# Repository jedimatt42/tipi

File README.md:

# TIPI

(Pronounced tip-ee)

Turn a Raspberry PI and some glue hardware into a TI Disk Drive and Network interface. 

Keep it open for further device extension.

## Branching

(For end users starting from an SD card image, you are already on the correct branch)

- End users must be on one of the `_release` branches for physical TIPI
- `main` branch is full of stuff that doesn't work, won't upgrade correctly, and certainly won't downgrade
- `main` branch is expert mode only

Branches:

```
  main - current development for latest Raspberry PI OS
  bookworm_release - Current release branch based on Raspberry PI OS 12 - bookworm
  bullseye_release - (legacy) end of life, as new bookworm_release branch is available
  buster_dev - (legacy) for patching upstream of buster_release
  buster_release - (legacy) for Raspberry PI 2W - 4B+ or Qemu use.
```

## Documentation

Please refer to the [wiki](https://github.com/jedimatt42/tipi/wiki)

## License 

The hardware design files and TI-99 DSR ROM code are in the [hardware](hardware) folder and free for use under the [UNLICENSE.txt](hardware/UNLICENSE.txt) 

The remaining software contained in this repository are licensed under the terms of [GPLv3](https://www.gnu.org/licenses/quick-guide-gplv3.en.html)

These files are part of TIPI.

TIPI is free hardware design and software: you can redistribute it and/or modify it under the terms of the GNU General Public License as published by the Free Software Foundation, either version 3 of the License, or (at your option) any later version.

TIPI is distributed in the hope that it will be useful, but WITHOUT ANY WARRANTY; without even the implied warranty of MERCHANTABILITY or FITNESS FOR A PARTICULAR PURPOSE.  See the GNU General Public License for more details.

You should have received a copy of the GNU General Public License along with TIPI SD Card Image.  If not, see [GNU Licenses](http://www.gnu.org/licenses/).

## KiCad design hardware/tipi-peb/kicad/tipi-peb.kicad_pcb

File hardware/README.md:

# Hardare design files for TIPI board and ROM driver software

This package below contains the hardware design files. These are un-encumbered open license files you can all do whatever you want with...

* tipi-peb - contains the PCB designs for the Periphal Expansion Box variant of the board. 
  * gerbers - artifacts for PCB fabrication
  * kicad - pcb schematic and layout design files for KiCad
  * ise - the verilog - Xilinx ISE 14.1 project files (use this with tipi-sideport design also)
* tipi-sideport - contains the PCB designs for the sideport board
  * gerbers - artifacts for PCB fabrication
  * kicad - pcb schematic and layout design files for KiCad
* tipi-speech - contains the PCB designs for the Speech Synthsizer Box variant of the TIPI board. 
  * gerbers - artifacts for PCB fabrication
  * kicad - pcb schematic and layout design files for KiCad
  * ise - the verilog - Xilinx ISE 14.1 project files (combined 32k and TIPI decoding)
* dsr - the ROM driver software for messaging to the PI and general DISK like behavior.

See [UNLICENSE.txt](UNLICENSE.txt)

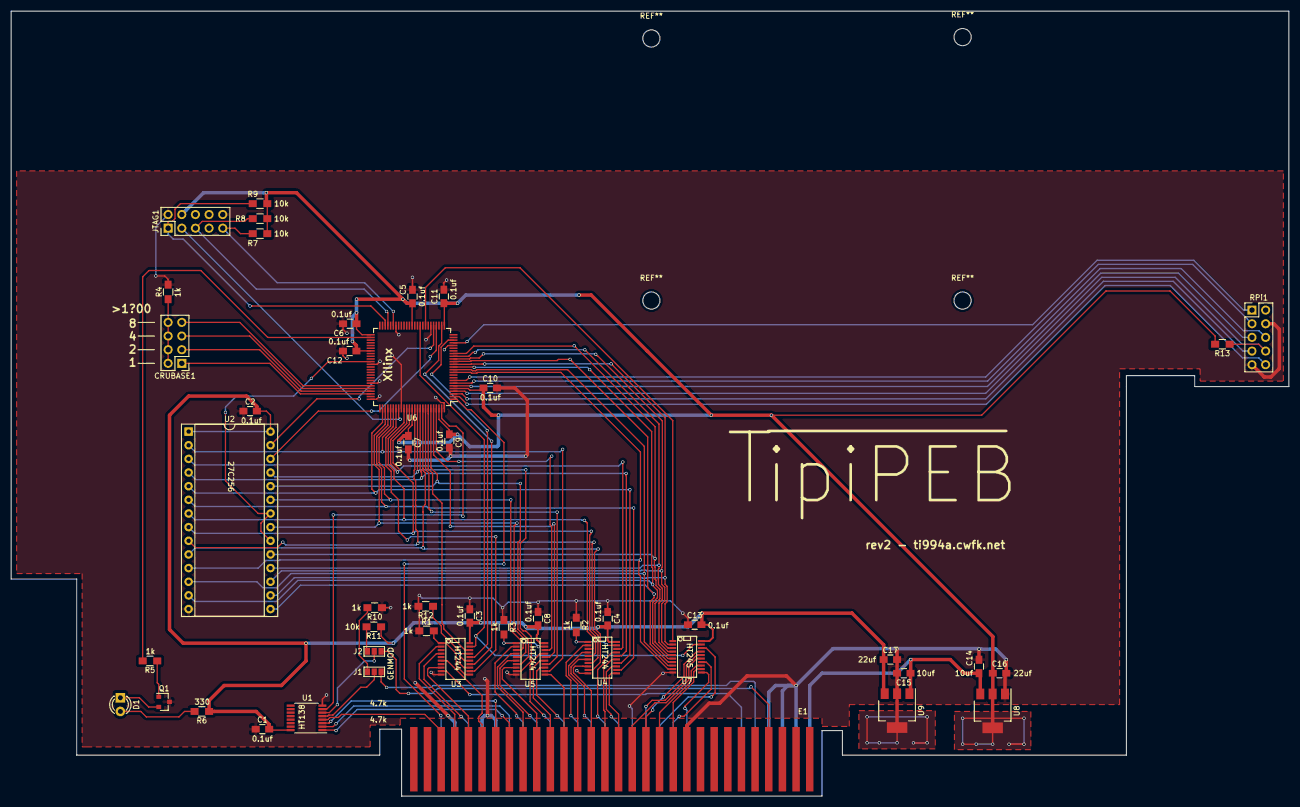
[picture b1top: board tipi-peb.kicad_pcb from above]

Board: 2 copper layers, 237.7 x 146.1 mm, 47 parts (0 on the bottom side), 102 nets.

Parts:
C1, C2, C3, C4, C5, C6, C7, C8, C9, C10, C11, C12, C13: 0.1uf; C_0805_HandSoldering
C14, C15: 10uf; C_0805_HandSoldering
C16, C17: 22uf; C_0805_HandSoldering
CRUBASE1: CONN_02X04; Pin_Header_Straight_2x04_Pitch2.54mm
D1: LED_ALT; LED_D3.0mm
E1: TiPEBEdge; ti99-peb-edge
J1, J2: GS3
JTAG1: AVR-JTAG-10; Pin_Header_Straight_2x05_Pitch2.54mm
Q1: Q_NPN_BCE; SOT-23
R1, R2, R3, R4, R5, R10, R12: 1k; R_0805_HandSoldering
R6: 330; R_0805_HandSoldering
R7, R8, R9, R11, R13: 10k; R_0805_HandSoldering
RPi1: RPI_CONN_02X05; Pin_Header_Straight_2x05_Pitch2.54mm
U1: 74HCT138; TSSOP-16_4.4x5mm_Pitch0.65mm
U2: 27C256; DIP-28_W15.24mm_Socket
U3, U4, U5: 74HCT244; SSOP-20
U6: XC95144XL-TQ100; TQFP-100_14x14mm_Pitch0.5mm
U7: 74HCT245; SSOP-20
U8: LM1117-3.3; SOT-223-3_TabPin2
U9: LM7805_TO220; SOT-223-3_TabPin2

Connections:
+3V3: C5.1, C6.1, C7.1, C9.1, C10.1, C11.1, C12.1, C16.1, JTAG1.4, R7.2, R8.2, R9.2, R13.2, U6.5, U6.26, U6.38, U6.51, U6.57, U6.88, U6.98, U8.2
+5V: C1.2, C2.2, C3.2, C4.2, C8.2, C13.2, C17.1, R6.1, R11.1, U1.16, U2.1, U2.28, U3.20, U4.20, U5.20, U7.20, U9.3
+8V: C14.1, C15.1, E1.1, U8.3, U9.1
B_A0: U5.18, U6.97
B_A1: U5.16, U6.96
B_A2: U5.14, U6.93
B_A3: U2.2, U5.12, U6.81
B_A4: U2.23, U5.3, U6.80
B_A5: U2.21, U5.5, U6.78
B_A6: U2.24, U5.7, U6.95
B_A7: U2.25, U5.9, U6.90
B_A8: U2.3, U4.18, U6.86
B_A9: U2.4, U4.16, U6.91
B_A10: U2.5, U4.14, U6.77
B_A11: U2.6, U4.12, U6.79
B_A12: U2.7, U4.3, U6.85
B_A13: U2.8, U4.5, U6.87
B_A14: U2.9, U4.7, U6.89
B_A15: U2.10, U4.9, U6.92
B_CRUCLK: U3.16, U6.23
B_DBIN: U3.12, U6.82
B_MEMEN: U1.7, U6.99
B_PH3: U3.14, U6.27
B_WE: U3.18, U6.94
CRUB_0: CRUBASE1.8, U6.70
CRUB_1: CRUBASE1.7, U6.71
CRUB_2: CRUBASE1.6, U6.72
CRUB_3: CRUBASE1.5, U6.73
DB_DIR: U6.33, U7.1
DB_EN: U3.19, U6.35, U7.19
DSR_B0: U2.26, U6.29
DSR_B1: U2.27, U6.30
DSR_EN: U2.20, U2.22, U6.61
GND: C1.1, C2.1, C3.1, C4.1, C5.2, C6.2, C7.2, C8.1, C9.2, C10.2, C11.2, C12.2, C13.1, C14.2, C15.2, C16.2, C17.2, E1.3, E1.5, E1.7, E1.20, E1.27, E1.47, E1.49, E1.53, JTAG1.2, JTAG1.10, Q1.3, R1.1, R2.1, R3.1, R4.2, R10.1, R12.2, RPi1.5, RPi1.9, U1.8, U2.14, U3.10, U4.10, U5.10, U6.21, U6.31, U6.44, U6.62, U6.69, U6.75, U6.84, U6.100, U7.10, U8.1, U9.2
JTAG_TCK: JTAG1.1, R9.1, U6.48
JTAG_TDI: JTAG1.9, R7.1, U6.45
JTAG_TDO: JTAG1.3, U6.83
JTAG_TMS: JTAG1.5, R8.1, U6.47
LED0: R5.2, U6.52
unnamed: CRUBASE1.1, CRUBASE1.2, CRUBASE1.3, CRUBASE1.4, R4.1
unnamed: D1.1, Q1.2
unnamed: D1.2, R6.2
unnamed: J1.1, R10.2
unnamed: J1.2, U1.5
unnamed: J2.1, R11.2
unnamed: J2.2, U1.6
unnamed: Q1.1, R5.1
unnamed: R1.2, U3.1, U3.11
unnamed: R2.2, U4.1, U4.19
unnamed: R3.2, U5.1, U5.19
unnamed: R12.1, U3.13, U3.15, U3.17
RDBENA: E1.11, U3.9
R_CLK: RPi1.1, U6.22
R_DC: RPi1.6, U6.2
R_DIN: R13.1, RPi1.7, U6.4
R_DOUT: RPi1.8, U6.7
R_LE: RPi1.3, U6.6
R_RESET: RPi1.4, U6.3
R_RT: RPi1.2, U6.8
TI_A0: E1.43, U5.2
TI_A1: E1.44, U5.4
TI_A2: E1.41, U5.6
TI_A3: E1.42, U5.8
TI_A4: E1.39, U5.17
TI_A5: E1.40, U5.15
TI_A6: E1.37, U5.13
TI_A7: E1.38, U5.11
TI_A8: E1.35, U4.2
TI_A9: E1.36, U4.4
TI_A10: E1.33, U4.6
TI_A11: E1.34, U4.8
TI_A12: E1.31, U4.17
TI_A13: E1.32, U4.15
TI_A14: E1.29, U4.13
TI_A15: E1.30, U4.11
TI_AMA: E1.46, U1.1
TI_AMB: E1.45, U1.2
TI_AMC: E1.48, U1.3
TI_AMD: E1.8, J2.3
TI_AME: E1.9, J1.3
TI_CRUCLK: E1.51, U3.4
TI_CRUIN: E1.55, U6.1
TI_D0: E1.28, U7.15
TI_D1: E1.25, U7.16
TI_D2: E1.26, U7.17
TI_D3: E1.23, U7.18
TI_D4: E1.24, U7.13
TI_D5: E1.21, U7.14
TI_D6: E1.22, U7.12
TI_D7: E1.19, U7.11
TI_DBIN: E1.52, U3.8
TI_MEMEN: E1.56, U1.4
TI_PH3: E1.50, U3.6
TI_WE: E1.54, U3.2
TP_D0: U2.11, U6.11, U7.9
TP_D1: U2.12, U6.12, U7.8
TP_D2: U2.13, U6.13, U7.6
TP_D3: U2.15, U6.15, U7.7
TP_D4: U2.16, U6.14, U7.2
TP_D5: U2.17, U6.16, U7.3
TP_D6: U2.18, U6.17, U7.4
TP_D7: U2.19, U6.18, U7.5

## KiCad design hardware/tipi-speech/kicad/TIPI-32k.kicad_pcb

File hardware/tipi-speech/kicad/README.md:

Hardare design files for VS-TIPI board

This package below contains the hardware design files. These are un-encumbered open license files you can all do whatever you want with...

    vs-tipi - contains the PCB designs for the Speech Synthsizer variant of the board.
        gerbers - artifacts for PCB fabrication
        kicad - pcb schematic and layout design files for KiCad
        ise - the verilog - Xilinx ISE 14.1 project files (use this with tipi-sideport design also)

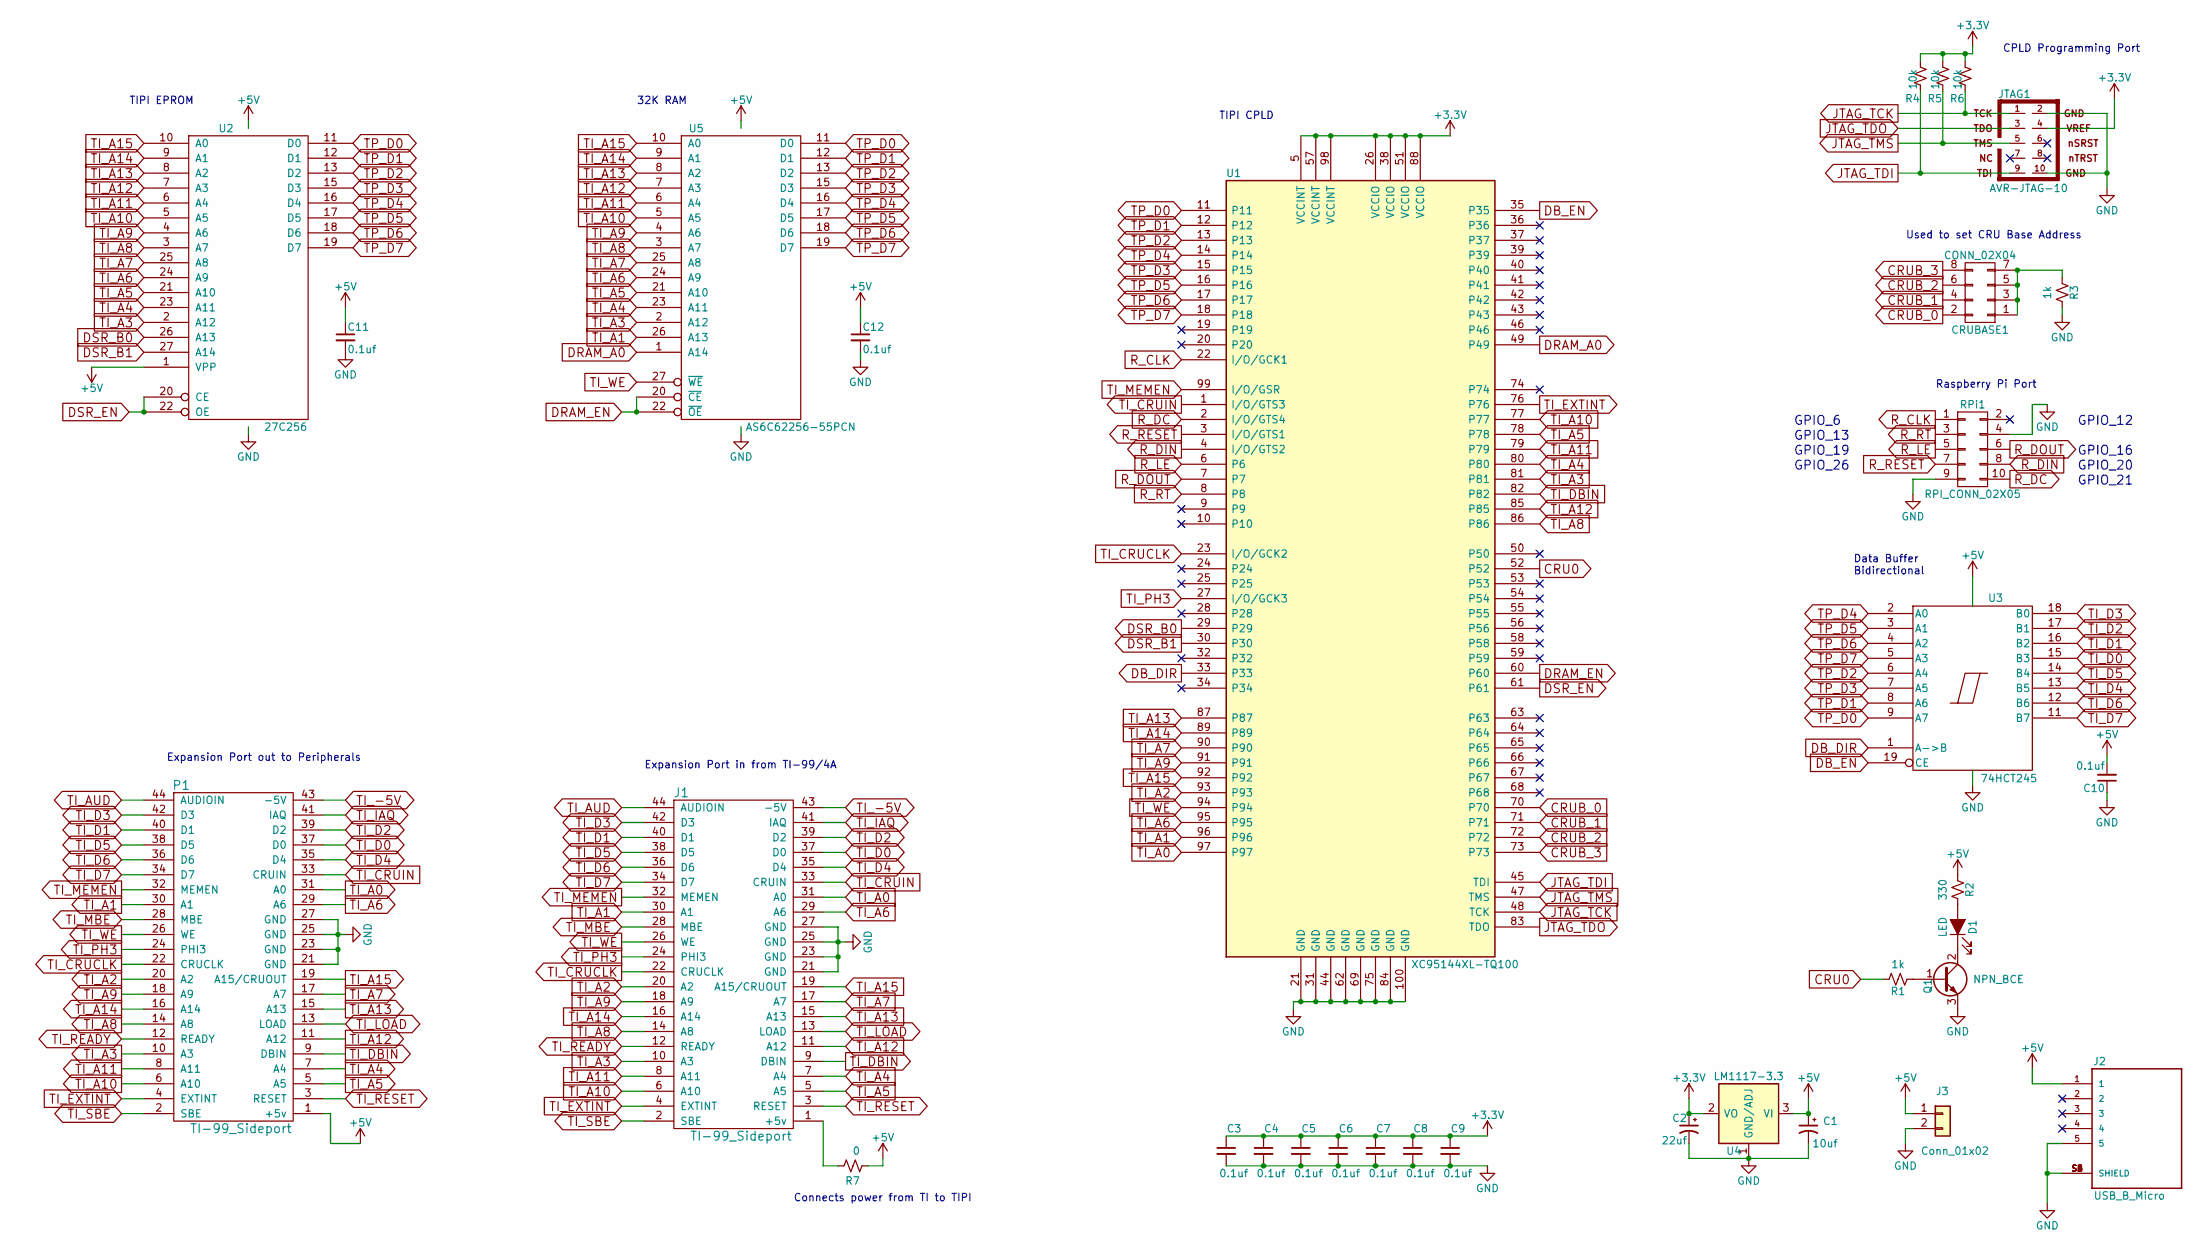
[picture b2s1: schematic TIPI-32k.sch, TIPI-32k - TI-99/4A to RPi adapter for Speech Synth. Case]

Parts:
C1: 10uf; C_0805_HandSoldering; LCSC C15850
C2: 22uf; C_0805_HandSoldering; LCSC C45783
C3, C6, C12: 0.1uf; C_0805_HandSoldering; LCSC C49678
C4, C5, C7, C8, C9, C10, C11: 0.1uf; C_0805_HandSoldering
CRUBASE1: CONN_02X04; Pin_Header_Straight_2x04_Pitch2.54mm
D1: LED; LED_D3.0mm
J1: TI-99_Sideport; ti99-exp-edge
J2: USB_B_Micro; AMPHENOL_10118194-0001LF; LCSC C132563
J3: Conn_01x02; PinHeader_1x02_P2.54mm_Horizontal
JTAG1: AVR-JTAG-10; IDC_Header_Straight_10pins
P1: TI-99_Sideport; ti99-exp-edge
Q1: NPN_BCE; SOT-23; LCSC C31776
R1, R3: 1k; R_0805_HandSoldering; LCSC C17513
R2: 330; R_0805_HandSoldering; LCSC C17630
R4, R5: 10k; R_0805_HandSoldering; LCSC C17414
R6: 10k; R_0805_HandSoldering
R7: 0; C_0805_HandSoldering
RPi1: RPI_CONN_02X05; IDC_Header_Straight_10pins
U1: XC95144XL-TQ100; TQFP-100_14x14mm_Pitch0.5mm; LCSC C45126
U2: 27C256; DIP-28_W15.24mm_Socket
U3: 74HCT245; SSOP-20; LCSC C5980
U4: LM1117-3.3; SOT-223; LCSC C23984
U5: AS6C62256-55PCN; DIP-28_W15.24mm_Socket

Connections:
+3V3: C2.1, C3.1, C4.1, C5.1, C6.1, C7.1, C8.1, C9.1, JTAG1.4, R4.2, R5.2, R6.2, U1.5 (VCCINT), U1.26 (VCCIO), U1.38 (VCCIO), U1.51 (VCCIO), U1.57 (VCCINT), U1.88 (VCCIO), U1.98 (VCCINT), U4.2 (VO), U4.4 (VO)
+5V: C1.1, C10.2, C11.1, C12.1, J2.1, J3.1, P1.1 (+5v), R2.1, R7.2, U2.1 (VPP), U2.28 (VCC), U3.20 (VCC), U4.3 (VI), U5.28 (VCC)
CRU0: R1.2, U1.52
CRUB_0: CRUBASE1.2, U1.70
CRUB_1: CRUBASE1.4, U1.71
CRUB_2: CRUBASE1.6, U1.72
CRUB_3: CRUBASE1.8, U1.73
DB_DIR: U1.33, U3.1 (A->B)
DB_EN: U1.35, U3.19 (CE)
DRAM_A0: U1.49, U5.1 (A14)
DRAM_EN: U1.60, U5.20 (~CE), U5.22 (~OE)
DSR_B0: U1.29, U2.26 (A13)
DSR_B1: U1.30, U2.27 (A14)
DSR_EN: U1.61, U2.20 (CE), U2.22 (OE)
GND: C1.2, C2.2, C3.2, C4.2, C5.2, C6.2, C7.2, C8.2, C9.2, C10.1, C11.2, C12.2, J1.21 (GND), J1.23 (GND), J1.25 (GND), J1.27 (GND), J2.5, J2.S1 (SHIELD), J2.S2 (SHIELD), J2.S3 (SHIELD), J2.S4 (SHIELD), J2.S5 (SHIELD), J2.S6 (SHIELD), J3.2, JTAG1.2, JTAG1.10, P1.21 (GND), P1.23 (GND), P1.25 (GND), P1.27 (GND), Q1.3 (E), R3.2, RPi1.4, RPi1.9, U1.21 (GND), U1.31 (GND), U1.44 (GND), U1.62 (GND), U1.69 (GND), U1.75 (GND), U1.84 (GND), U1.100 (GND), U2.14 (GND), U3.10 (GND), U4.1 (GND/ADJ), U5.14 (GND)
JTAG_TCK: JTAG1.1, R6.1, U1.48 (TCK)
JTAG_TDI: JTAG1.9, R4.1, U1.45 (TDI)
JTAG_TDO: JTAG1.3, U1.83 (TDO)
JTAG_TMS: JTAG1.5, R5.1, U1.47 (TMS)
unnamed: CRUBASE1.1, CRUBASE1.3, CRUBASE1.5, CRUBASE1.7, R3.1
unnamed: D1.1 (K), Q1.2 (C)
unnamed: D1.2 (A), R2.2
unnamed: J1.1 (+5v), R7.1
unnamed: Q1.1 (B), R1.1
R_CLK: RPi1.1, U1.22 (I/O/GCK1)
R_DC: RPi1.10, U1.2 (I/O/GTS4)
R_DIN: RPi1.8, U1.4 (I/O/GTS2)
R_DOUT: RPi1.6, U1.7
R_LE: RPi1.5, U1.6
R_RESET: RPi1.7, U1.3 (I/O/GTS1)
R_RT: RPi1.3, U1.8
TI_-5V: J1.43 (-5V), P1.43 (-5V)
TI_A0: J1.31 (A0), P1.31 (A0), U1.97
TI_A1: J1.30 (A1), P1.30 (A1), U1.96, U5.26 (A13)
TI_A2: J1.20 (A2), P1.20 (A2), U1.93
TI_A3: J1.10 (A3), P1.10 (A3), U1.81, U2.2 (A12), U5.2 (A12)
TI_A4: J1.7 (A4), P1.7 (A4), U1.80, U2.23 (A11), U5.23 (A11)
TI_A5: J1.5 (A5), P1.5 (A5), U1.78, U2.21 (A10), U5.21 (A10)
TI_A6: J1.29 (A6), P1.29 (A6), U1.95, U2.24 (A9), U5.24 (A9)
TI_A7: J1.17 (A7), P1.17 (A7), U1.90, U2.25 (A8), U5.25 (A8)
TI_A8: J1.14 (A8), P1.14 (A8), U1.86, U2.3 (A7), U5.3 (A7)
TI_A9: J1.18 (A9), P1.18 (A9), U1.91, U2.4 (A6), U5.4 (A6)
TI_A10: J1.6 (A10), P1.6 (A10), U1.77, U2.5 (A5), U5.5 (A5)
TI_A11: J1.8 (A11), P1.8 (A11), U1.79, U2.6 (A4), U5.6 (A4)
TI_A12: J1.11 (A12), P1.11 (A12), U1.85, U2.7 (A3), U5.7 (A3)
TI_A13: J1.15 (A13), P1.15 (A13), U1.87, U2.8 (A2), U5.8 (A2)
TI_A14: J1.16 (A14), P1.16 (A14), U1.89, U2.9 (A1), U5.9 (A1)
TI_A15: J1.19 (A15/CRUOUT), P1.19 (A15/CRUOUT), U1.92, U2.10 (A0), U5.10 (A0)
TI_AUD: J1.44 (AUDIOIN), P1.44 (AUDIOIN)
TI_CRUCLK: J1.22 (CRUCLK), P1.22 (CRUCLK), U1.23 (I/O/GCK2)
TI_CRUIN: J1.33 (CRUIN), P1.33 (CRUIN), U1.1 (I/O/GTS3)
TI_D0: J1.37 (D0), P1.37 (D0), U3.15 (B3)
TI_D1: J1.40 (D1), P1.40 (D1), U3.16 (B2)
TI_D2: J1.39 (D2), P1.39 (D2), U3.17 (B1)
TI_D3: J1.42 (D3), P1.42 (D3), U3.18 (B0)
TI_D4: J1.35 (D4), P1.35 (D4), U3.13 (B5)
TI_D5: J1.38 (D5), P1.38 (D5), U3.14 (B4)
TI_D6: J1.36 (D6), P1.36 (D6), U3.12 (B6)
TI_D7: J1.34 (D7), P1.34 (D7), U3.11 (B7)
TI_DBIN: J1.9 (DBIN), P1.9 (DBIN), U1.82
TI_EXTINT: J1.4 (EXTINT), P1.4 (EXTINT), U1.76
TI_IAQ: J1.41 (IAQ), P1.41 (IAQ)
TI_LOAD: J1.13 (LOAD), P1.13 (LOAD)
TI_MBE: J1.28 (MBE), P1.28 (MBE)
TI_MEMEN: J1.32 (MEMEN), P1.32 (MEMEN), U1.99 (I/O/GSR)
TI_PH3: J1.24 (PHI3), P1.24 (PHI3), U1.27 (I/O/GCK3)
TI_READY: J1.12 (READY), P1.12 (READY)
TI_RESET: J1.3 (RESET), P1.3 (RESET)
TI_SBE: J1.2 (SBE), P1.2 (SBE)
TI_WE: J1.26 (WE), P1.26 (WE), U1.94, U5.27 (~WE)
TP_D0: U1.11, U2.11 (D0), U3.9 (A7), U5.11 (D0)
TP_D1: U1.12, U2.12 (D1), U3.8 (A6), U5.12 (D1)
TP_D2: U1.13, U2.13 (D2), U3.6 (A4), U5.13 (D2)
TP_D3: U1.15, U2.15 (D3), U3.7 (A5), U5.15 (D3)
TP_D4: U1.14, U2.16 (D4), U3.2 (A0), U5.16 (D4)
TP_D5: U1.16, U2.17 (D5), U3.3 (A1), U5.17 (D5)
TP_D6: U1.17, U2.18 (D6), U3.4 (A2), U5.18 (D6)
TP_D7: U1.18, U2.19 (D7), U3.5 (A3), U5.19 (D7)

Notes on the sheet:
GPIO_21
GPIO_20
GPIO_16
GPIO_12
GPIO_6
GPIO_13
GPIO_19
GPIO_26
Expansion Port in from TI-99/4A
Expansion Port out to Peripherals
Connects power from TI to TIPI
TIPI EPROM
32K RAM
TIPI CPLD
CPLD Programming Port
Used to set CRU Base Address
Raspberry Pi Port
Data Buffer Bidirectional

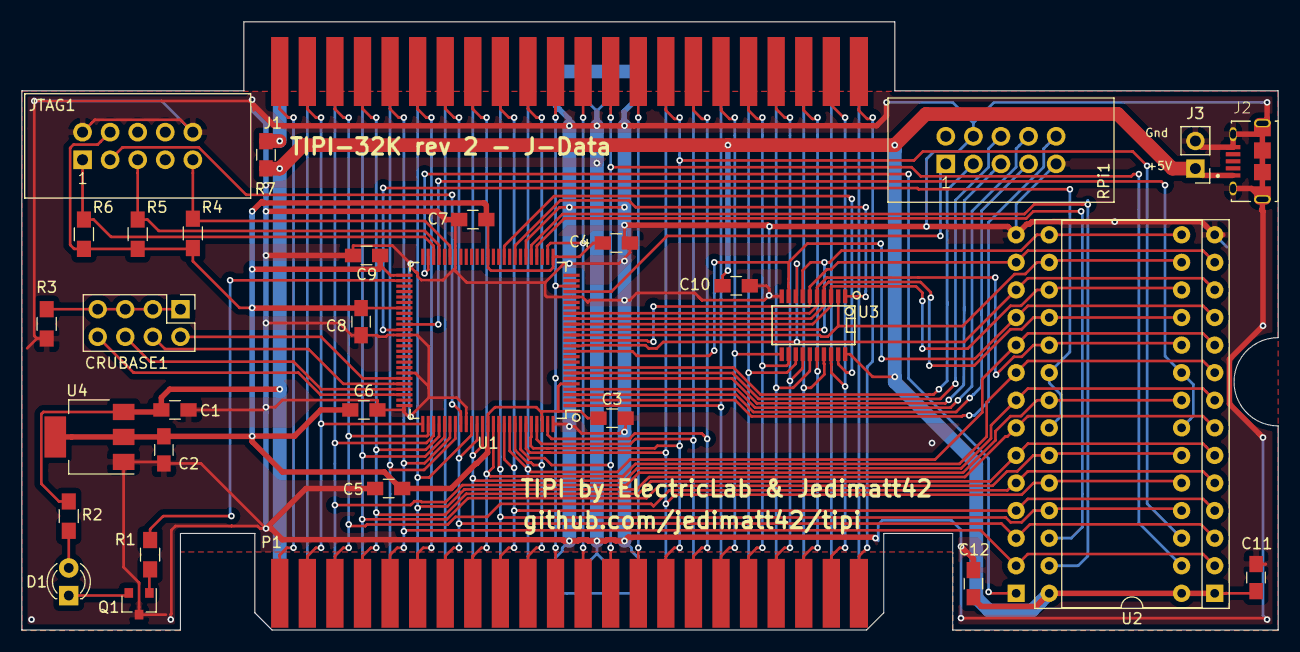
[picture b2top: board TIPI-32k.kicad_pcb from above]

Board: 2 copper layers, 115.7 x 56.0 mm, 33 parts (1 on the bottom side), 78 nets.

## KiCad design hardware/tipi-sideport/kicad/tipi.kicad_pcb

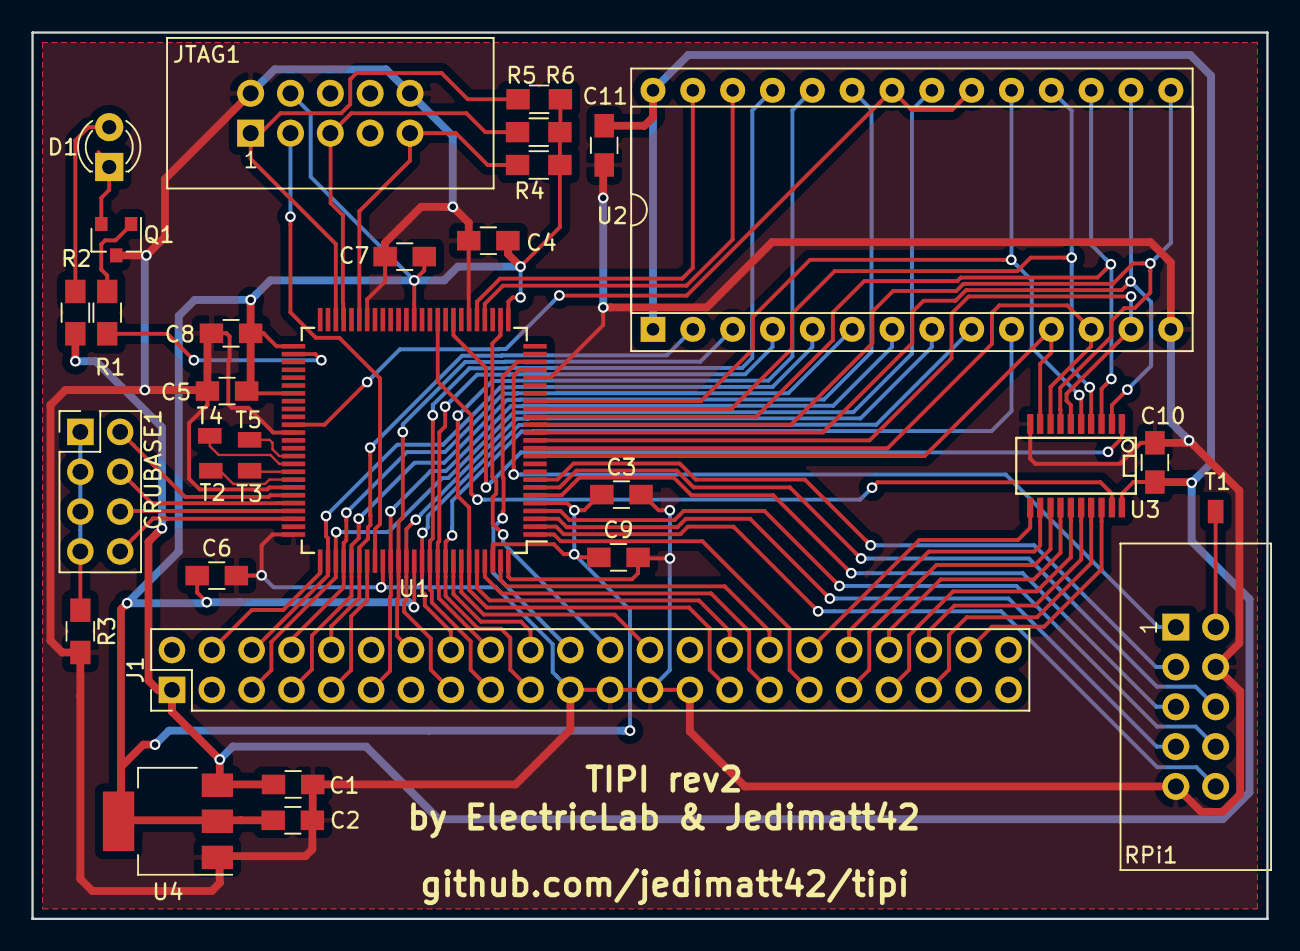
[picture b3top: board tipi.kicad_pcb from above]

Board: 2 copper layers, 78.7 x 56.5 mm, 32 parts (0 on the bottom side), 72 nets.

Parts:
C1: 10uf; C_0805_HandSoldering
C2: 22uf; C_0805_HandSoldering
C3, C4, C5, C6, C7, C8, C9, C10, C11: 0.1uf; C_0805_HandSoldering
CRUBASE1: CONN_02X04; Pin_Header_Straight_2x04_Pitch2.54mm
D1: LED_ALT; LED_D3.0mm
J1: TI32kSideport; Pin_Header_Straight_2x22_Pitch2.54mm
JTAG1: AVR-JTAG-10; IDC_Header_Straight_10pins
Q1: Q_NPN_BCE; SOT-23
R1, R3: 1k; R_0805_HandSoldering
R2: 330; R_0805_HandSoldering
R4, R5, R6: 10k; R_0805_HandSoldering
RPi1: RPI_CONN_02X05; IDC_Header_Straight_10pins
T1, T2, T3, T4, T5: TEST_1P; SolderWirePad_single_0-8mmDrill
U1: XC95144XL-TQ100; TQFP-100_14x14mm_Pitch0.5mm
U2: 27C256; DIP-28_W15.24mm_Socket
U3: 74HCT245; SSOP-20
U4: LM1117-3.3; SOT-223

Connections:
+3V3: C2.1, C3.1, C4.1, C5.1, C6.1, C7.1, C8.1, C9.1, JTAG1.4, R4.2, R5.2, R6.2, U1.5, U1.26, U1.38, U1.51, U1.57, U1.88, U1.98, U4.2, U4.4
+5V: C1.1, C10.2, C11.2, J1.1, R2.1, U2.1, U2.28, U3.20, U4.3
CRU0: R1.2, U1.52
CRUB_0: CRUBASE1.2, U1.70
CRUB_1: CRUBASE1.4, U1.71
CRUB_2: CRUBASE1.6, U1.72
CRUB_3: CRUBASE1.8, U1.73
DB_DIR: U1.33, U3.1
DB_EN: U1.35, U3.19
DSR_B0: U1.29, U2.26
DSR_B1: U1.30, U2.27
DSR_EN: U1.61, U2.20, U2.22
GND: C1.2, C2.2, C3.2, C4.2, C5.2, C6.2, C7.2, C8.2, C9.2, C10.1, C11.1, J1.21, J1.23, J1.25, J1.27, JTAG1.2, JTAG1.10, Q1.3, R3.2, RPi1.4, RPi1.9, U1.21, U1.31, U1.44, U1.62, U1.69, U1.75, U1.84, U1.100, U2.14, U3.10, U4.1
JTAG_TCK: JTAG1.1, R6.1, U1.48
JTAG_TDI: JTAG1.9, R4.1, U1.45
JTAG_TDO: JTAG1.3, U1.83
JTAG_TMS: JTAG1.5, R5.1, U1.47
unnamed: CRUBASE1.1, CRUBASE1.3, CRUBASE1.5, CRUBASE1.7, R3.1
unnamed: D1.1, Q1.2
unnamed: D1.2, R2.2
unnamed: Q1.1, R1.1
unnamed: RPi1.2, T1.1
unnamed: T2.1, U1.68
unnamed: T3.1, U1.67
unnamed: T4.1, U1.66
unnamed: T5.1, U1.65
R_CLK: RPi1.1, U1.22
R_DC: RPi1.10, U1.2
R_DIN: RPi1.8, U1.4
R_DOUT: RPi1.6, U1.7
R_LE: RPi1.5, U1.6
R_RESET: RPi1.7, U1.3
R_RT: RPi1.3, U1.8
TI_A0: J1.31, U1.97
TI_A1: J1.30, U1.96
TI_A2: J1.20, U1.93
TI_A3: J1.10, U1.81, U2.2
TI_A4: J1.7, U1.80, U2.23
TI_A5: J1.5, U1.78, U2.21
TI_A6: J1.29, U1.95, U2.24
TI_A7: J1.17, U1.90, U2.25
TI_A8: J1.14, U1.86, U2.3
TI_A9: J1.18, U1.91, U2.4
TI_A10: J1.6, U1.77, U2.5
TI_A11: J1.8, U1.79, U2.6
TI_A12: J1.11, U1.85, U2.7
TI_A13: J1.15, U1.87, U2.8
TI_A14: J1.16, U1.89, U2.9
TI_A15: J1.19, U1.92, U2.10
TI_CRUCLK: J1.22, U1.23
TI_CRUIN: J1.33, U1.1
TI_D0: J1.37, U3.15
TI_D1: J1.40, U3.16
TI_D2: J1.39, U3.17
TI_D3: J1.42, U3.18
TI_D4: J1.35, U3.13
TI_D5: J1.38, U3.14
TI_D6: J1.36, U3.12
TI_D7: J1.34, U3.11
TI_DBIN: J1.9, U1.82
TI_EXTINT: J1.4, U1.76
TI_MEMEN: J1.32, U1.99
TI_PH3: J1.24, U1.27
TI_WE: J1.26, U1.94
TP_D0: U1.11, U2.11, U3.9
TP_D1: U1.12, U2.12, U3.8
TP_D2: U1.13, U2.13, U3.6
TP_D3: U1.15, U2.15, U3.7
TP_D4: U1.14, U2.16, U3.2
TP_D5: U1.16, U2.17, U3.3
TP_D6: U1.17, U2.18, U3.4
TP_D7: U1.18, U2.19, U3.5

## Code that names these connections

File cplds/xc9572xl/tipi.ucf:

NET "cru0" LOC = P13;

NET "crub<0>" LOC = P09;
NET "crub<1>" LOC = P10;
NET "crub<2>" LOC = P11;
NET "crub<3>" LOC = P12;

NET "db_dir" LOC = P57;
NET "db_en" LOC = P56;
NET "dsr_b0" LOC = P06;
NET "dsr_b1" LOC = P07;
NET "dsr_en" LOC = P08;

NET "r_clk" LOC = P15;
NET "r_dc" LOC = P25;
NET "r_dout" LOC = P20;
NET "r_le" LOC = P19;
NET "r_rt" LOC = P18;
NET "r_din" LOC = P24;
NET "r_reset" LOC = P23;

// NET "spare_2" LOC = PO2;
// NET "spare_22" LOC = P22;
// NET "spare_5" LOC = P05;
// NET "spare_64" LOC = P64;

NET "ti_cruclk" LOC = P16;
NET "ti_cruin" LOC = P52;
NET "ti_dbin" LOC = P35;
NET "ti_extint" LOC = P31;
NET "ti_memen" LOC = P51;
NET "ti_ph3" LOC = P17;
NET "ti_we" LOC = P47;

NET "ti_a<0>" LOC = P50;
NET "ti_a<1>" LOC = P49;
NET "ti_a<2>" LOC = P46;
NET "ti_a<3>" LOC = P36;
NET "ti_a<4>" LOC = P33;
NET "ti_a<5>" LOC = P32;
NET "ti_a<6>" LOC = P48;
NET "ti_a<7>" LOC = P43;
NET "ti_a<8>" LOC = P39;
NET "ti_a<9>" LOC = P44;
NET "ti_a<10>" LOC = P27;
NET "ti_a<11>" LOC = P34;
NET "ti_a<12>" LOC = P38;
NET "ti_a<13>" LOC = P40;
NET "ti_a<14>" LOC = P42;
NET "ti_a<15>" LOC = P45;

NET "tp_d<0>" LOC = P62;
NET "tp_d<1>" LOC = P63;
NET "tp_d<2>" LOC = P04;
NET "tp_d<3>" LOC = P01;
NET "tp_d<4>" LOC = P60;
NET "tp_d<5>" LOC = P61;
NET "tp_d<6>" LOC = P59;
NET "tp_d<7>" LOC = P58;

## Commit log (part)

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2020-07-03 should rebuild libtipi for 2.1
2020-07-03 remove outdated arg for samba
2020-07-05 release native extensions for DV80 TIFILES
2020-07-10 Fix emulated mouse buttons PS/2 protocol
2020-07-11 rebuild deps for <= 2.4
2020-07-12 fix unicode handling in linux file names
    Now if there is any unicode or the name is longer than 10 characters,
    the full name is processed by the CRC15 to come up with the hash suffix.
    the full name is transliterated to approximate single byte characters
    for any unicode character, and then the prefix is take from that.
2020-07-12 fix SNEK
    some programs used >127 characters so encoding of the strings needed
    to be latin1 not ascii. (ascii is just 0-127)
2020-07-23 lighter patch, and version rolling
2020-07-26 non-dv80 files should be ignored as TIPI mapping
    fix issue #121
2020-09-22 fix PI.PIO setup mistake
    I manually cloned the PrinterToPDF repo, consequently the old
    post-upgrade.sh would skip building it... This change, triggers on
    the build artifact, not just the directory
2020-10-05 fix trailing whitespace in names
2020-11-04 fix native file handling, and off by one eof in VARIABLE record files.
2020-11-07 patch the broken fiads
2020-11-08 re-run the fiad fix for variable record files
2020-12-12 update version for timestamp release
2020-12-19 release a fix for relative record file growth
2020-12-25 sort directory entries in catalog first by default.
    PI.CONFIG DIR_SORT entry can have values MIXED, FIRST, or LAST to
    control placement of directories in the catalog order.
2020-12-27 fix setPATH to not expect unit 0 to be mapped, and not care about old path existing.
2020-12-27 a couple fixes for release
2021-01-10 archive step to ensure wifi works
2021-01-29 update to main epson to PDF code from RWAP
2021-01-31 adjust us paper size and margins
2021-02-03 release 2.18 update printer conversion and add UDP socket support
2021-02-24 fixed record files should use the record number
    from the pab, most of the time.
2021-02-25 release
2021-03-03 damnit.
2021-04-13 wait loop in powerup to very restart
    Send the 0xF1 ack message
    Wait a bit to see if we get it back. But don't wait forever.
    Then reset the TipiService via cru pulse.
    Then, wait for RCIN to be 0x00 before returning to console
    powerup sequence.
2021-04-16 let tipi.service restart on reset storms
2021-04-17 less logging on tipimon.service startup
2021-04-20 just extend the reset cru signal period
2021-06-29 include tipi xb mouse driver on every TIPI. drive
2021-08-02 detect error posting to PI.HTTP
2021-09-06 role version for release
    writing to HTTP(S) if server supports it.
    TLS sockets vi PI.TLS or messaging 0x24
2021-11-04 respect protect flag on open, save, and delete
2021-11-04 releaseable
2021-11-05 remove i2c setup steps
2021-11-20 script to create a tipi backup archive
2021-11-20 watch /tmp/tipi_backup to detect completion
2021-11-21 cleanup restore archive in /boot
    so it doesn't keep applying
2021-11-21 change branch name
2021-11-21 use the timestamp in the filename
2022-01-03 do not scale mouse movement
2022-01-03 update for right mouse button support
2022-01-20 fix for multple incoming client sockets
    handleAccept would hang if id 1 was used already. It should
    have incremented the id and tried 2, 3, etc..
2022-01-31 not released yet
2022-02-03 release date
2022-02-11 experiment with TIPI_SIG_DELAY
2022-02-11 small releasable tweak for TIPI_SIG_DELAY
2022-03-07 prepare release for js99er async fix from PeteE
2022-03-07 quiet nonsense error when cataloging
2022-03-13 implement ?W native DISPLAY file writing
    PI.CONFIG HOST_EOL can be set to CRLF or LF to control file line ending
2022-03-16 fix header during rename, limit dio to sectors
2022-03-19 fix end limit check on directInput/Output
2022-03-20 tweaks for different emulator integration options
2022-03-21 show and allow changing drive mappings from webui
2022-03-21 websocket_readMsg must not return NULL
    The calling functions do not handle timeout exception gracefully
2022-04-02 readme around emulation
2022-04-05 debugging tool
2022-04-10 split gpio and websocket libraries
    can run natively on linux x86... woot
    library is selected at runtime based on
    configuration.
    gpio is only built if on a Raspberry PI OS
2022-04-10 fix typos and ignore some noise
2022-04-10 fix wiringPi dependency
2022-04-12 set 3 key paths as environment variables
    use it enough to get TIPICFG to work
2022-04-15 use base dirs from env vars
2022-04-16 hide a user config file for paths
    see jm42/alt_paths branch
2022-04-16 this actually works
    only the primary tipi service is running, so none of the
    extra features like the web-ui, tipi-monitor, tipi-super services
    are there... this impacts features like DSK extraction and upgrade
    more to come
2022-04-23 start other services that run as user 'tipi'
2022-04-23 expose webui port
2022-05-22 maybe useful tool
2022-07-19 LVL2 sector read write
2022-07-20 web ui mapped drives are now links to mapped directory
2022-07-23 set version for release of sector io
2022-07-30 handle possible exception in reading networks
2022-09-03 what happens after opening and saving in Kicad 6
2022-10-11 magic conversion to kicad 6
2022-10-15 use scripts via usbmount to bind mount
    these need to be installed into /etc/usbmount/mount.d and umount.d
    respectively.
2022-10-16 restart udev service with config update
2023-01-01 quick pass as using kernel module instead of WiringPI
2023-01-01 use exported sysfs tipi_reset with irq
    make sure /dev/tipi_control and /dev/tipi_data are
    readable on boot
2023-01-01 one less type warning
2023-01-21 creating branch for buster patching
    the branch `main` will no longer be for `buster` developement. It will
    be focused on `bullseye` development.
    Use this `buster_dev` branch for patches to keep buster working if
    necessary. `buster_release` will become downstream of this `buster_dev`
    branch.
2023-01-21 remove old wiringPi libtipi library
2023-01-21 set upgrade branch name
2023-01-21 refix branch name after merge from main
2023-01-27 make kernel devices accessible after module rebuild
2023-01-28 some dependencies that shouldn't be assumed
2023-01-29 temporary while figuring out edge detection
    On the Le Potato, the kernel module didn't enable
    the edge detection control file... hmmm
2023-01-29 my aarch64 fix for PrinterToPDF was accepted
2023-02-14 fix backups so the browser doesn't uncompress them
2023-02-26 restrict search to filename not dirs
2023-03-06 fix path query params for BASIC edit request
2023-03-18 i2c config step
2023-04-01 fix PI.HTTP urls with query parameters
2023-04-01 hint when disabling emulation to restart service
2023-04-01 Revert "fix backup download content type"
    This reverts commit f1aec48b6d815426317265527bee18e22811e08d.
2023-04-01 allow deleting archives from the backup list
2023-04-02 fix branch display on about page
2023-04-08 allow ?J native flag on PI.HTTP curlfiles
    - add error handling
    - delegate write operation to open_file type
    - allow the flag and pass it through for CurlFile
2023-04-14 Allow `#?` wildcard when file/dir name part matching
2023-04-15 unwrap arrays into records for JsonFile processing
2023-04-15 fix string handling
2023-04-15 non-ssl link to js99er.net
2023-04-22 refinement after testing
2023-04-23 release 3.9
    - add NATIVE_TEXT_DIRS to PI.CONFIG
    - allow opening PI.CONFIG with record length of 80 - 254 for longer
    values
2023-04-24 Pack native .fb files into Forth blocks
    rough draft, seems to work.
    This is a read-only operation. Native text files ending in the `.fb` suffix
    can be loaded as a packed set of blocks into FbForth. Should work with other
    DISPLAY/FIXED 128 type forth variants on the 4A as well, such as TurboForth.
    ```
    USEBFL TIPI.4TH/FB
2023-04-24 fix corner case where user has a directory named TIPI
2023-04-29 a start on level 2 IO for native files
2023-04-29 make TIFILES headers have precedence have CatalogFiles respects NATIVE_TEXT_DIRS
2023-05-01 remove unnecessary and wrong bytes to block to bytes calculation
    tweak the logging on error to be less cryptic
2023-05-04 allow direct-input of native DIS/FIX 128 files
    which implies that they can be copied from TIPI to
    other media.
2023-05-04 quiet some logging
2023-05-06 fix URIx and ?J usage
2023-05-06 improve restore workflow
    - validate tar is a tipi backup before extracting
    - provide status / result of validation or extraction in webui
    - upload tolerates any .tar.gz in.
    - File name no longer has to start with tipi-backup, or have a timestamp in the name.
2023-05-06 fix block rounding for direct-input again.
2023-05-07 only save to text for direct-output if DV80
2023-07-10 a few notes on initial SD card setup for distribution
2023-07-10 show perceived native file type based on NATIVE_TEXT_DIRS config
2023-07-14 rev verson for release
2023-07-29 add TAP device so that TIPI might handle tape programs
    TI tape device name is CS1
    Add a 3 character device name TAP so that a simple hex edit of a
    program or cartridge bin could have a change and sending it's io
    to TIPI.
2023-07-29 Enable handling CS1 requests
    CS1_FILE can be set in PI.CONFIG
    If CS1_FILE is not set, then TIPI will return 'pass' so
    that the console DSRLNK can continue searching and go on
    to the GROM CS1 DSR.
    If it is set, then file operations will act on that file
    as though it was a TIPI disk operation.
2023-07-29 allow setting CS1_FILE mapping from TIPICFG
2023-07-31 add DSK5-9 DSR headers
2023-08-04 release version - CS1 and DSK5-9
2023-08-20 release tipiwatchdog fix
2023-09-03 implement mfm 16 sec/track format
2023-09-04 oops, I missed a call point that I renamed
2023-10-01 release updated tipicfg
2023-11-05 fix error handling
2023-12-09 setting to control if TIPI restores TIPICFG and TELNET on boot
2023-12-10 tipicfg cleanup
2024-01-06 adapt install procedure for Raspbian bookworm edition
2024-05-08 kernel upgrades need too much space to keep /var/tmp as tmpfs
2024-05-10 restore branch to main
2024-05-10 no need to mount if we are just going to reboot
2024-06-01 Update version.txt for bookworm
2024-06-16 fix pab sent to TIPI to not have cpuflag bit set
    TIPI doesn't need to know where anything lives in the 4A's memory
    also abstract the functions to delegate for vdp or cpu transfer
2024-06-16 just a comment update about register usage
2024-06-19 reset branch to 'main' on main
2024-06-19 4.1
    - fix web-ui log viewing
    - fix setting WiFi from PI.CONFIG ( TIPICFG )
    - delegates to raspi-config noint
    - retries upto 5 times cause networks can be elusive
    - can edit the SSID in TIPICFG, to the same value, and will re-submit
    when 'W'rite is requested.
2024-06-21 v 4.2, TIPICFG v14
    Update TIPICFG to support spaces in SSID and PSK
2024-06-30 hide clang linter cache
2024-07-13 more idle time while idle, reduce cpu usage to 10-15% while idle
2024-07-21 raise SoftResetException on RESET
2024-08-24 cpu buffer support for lvl3 routines, and lvl2 io. modeled from the Myarc HFDC manual. Does not support PABs in CPU memory, but the buffers referred to in PABs and in lvl2 params can be set to cpu me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
2024-12-24 add page in web-ui to edit PI.CONFIG
2024-12-30 on file not found, default to ERROR
2024-12-30 disable file operations based on selections
2024-12-30 pi.config input validation
2024-12-31 rename functionality
2025-01-05 cleanup unused icons
2025-02-02 fix code label at odd address
2025-02-15 Fix file not found behavior
    If lvl3_not_found config item is set to ERROR
    when drive is not mapped, pass to other controller
    when drive is mapped, error
    If lvl3_not_found config item is set to PASS
    when drive is not mapped, pass to other controler
    when drive is mapped, also pass to other controller
2025-02-16 setup sd card images with telnetd-ssl
2025-02-17 circling the perimeter
2025-02-17 pasted the old version earlier
2025-02-19 custom message handlers in /home/tipi/plugins
2025-02-22 first pass at reloading extensions
2025-02-22 reliable method of plugin reloading
2025-02-22 stub for KeyboardPlugin
2025-02-22 map usb keycodes to ascii
2025-02-22 handle punctuation
2025-02-22 example description
2025-02-22 less log noise
2025-02-23 it synthesises and fits
2025-03-02 test read RD and RC
2025-03-02 manage states differently
2025-03-02 working read/write and test of tipi_4bit_pi_bus
2025-03-09 add test for crubits module
2025-03-09 pull in prior work on test_crubits
2025-03-09 import more tests from old project
2025-03-09 shifting back to vscode to fix indentations
2025-03-22 comments, comments, comments
2025-03-23 a little more test, a little more cleanup
2025-04-21 add test for led
2025-04-28 remove a little unused terms
2025-08-03 no-more-kofi
2025-08-27 4.7 - a few minor fixes
2025-08-29 tipimon.service rebuilds cache on startup

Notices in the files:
hardware/tipi-speech/kicad/TIPI-32k.kicad_pcb:
(C) 1983 - J-Data (Open source actually)
